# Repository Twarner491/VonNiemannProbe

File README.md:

# Von Niemann Probe
### Devoloped by [Teddy Warner](https://teddywarner.org/About-Me/about/) and [Jack Hollingsworth](http://fabacademy.org/2021/labs/charlotte/students/jack-hollingsworth/about/).

**An AVR-based Bluetooth telegraphing shoe insole that lets you play chess in the way Hans Niemann has been accused!** This project is our contribution to the ongoing investigation into the Hans Niemann / Magnus Carlsen cheating scandal and tests the feasibility of creating and using an over-the-board chess cheating aid.

### Check out the Von Niemann Probe's documentation on [TeddyWarner.org](https://teddywarner.org/Projects/VonNiemannProbe/)!

**© Teddy Warner & Jack Hollingsworth- 2022**
> This work may be reproduced, modified, distributed, performed, and displayed for any purpose,
> but must acknowledge Teddy Warner. Copyright is retained and must be preserved. 
> The work is provided as is; no warranty is provided, and users accept all liability.

### Sponsor -

## Python Dependencies - 

Various Python dependencies are needed to run the VNPFinal.py script, but overall the installation is pretty lightweight. The only change that needs to be made locally is the path of your stockfish .exe, which must be downloaded from [here](https://stockfishchess.org/download/) prior to use. Any version of Stockfish should work, but we have only tested on the latest version (Version 15). 
<br/><br/>
The outgoing COM port of the Bluetooth module must be updated, this can be found in device manager in all Windows 7+ machines. 
Install commands for all Python dependencies are below, any release past Python 3.7 will work.

```python
pip install stockfish
pip install python-chess
pip install pyserial
pip install regex
```

## Sources -
- [https://www.npr.org/2022/10/21/1130442319/hans-niemann-sues-magnus-carlsen-for-100-million-accusing-him-of-defamation](https://www.npr.org/2022/10/21/1130442319/hans-niemann-sues-magnus-carlsen-for-100-million-accusing-him-of-defamation)
- [https://youtu.be/eg5G1A_mTFg](https://youtu.be/eg5G1A_mTFg)
- [https://twitter.com/hansmokeniemann](https://twitter.com/hansmokeniemann)
- [https://futurism.com/von-neumann-probe](https://futurism.com/von-neumann-probe)
- [https://ww1.microchip.com/downloads/en/DeviceDoc/ATtiny212-412-DataSheet-DS40001911B.pdf](https://ww1.microchip.com/downloads/en/DeviceDoc/ATtiny212-412-DataSheet-DS40001911B.pdf)
- [https://components101.com/sites/default/files/component_datasheet/HC06%20Bluetooth%20Module%20Datasheet.pdf](https://components101.com/sites/default/files/component_datasheet/HC06%20Bluetooth%20Module%20Datasheet.pdf)
- [https://components101.com/wireless/hc-06-bluetooth-module-pinout-datasheet](https://components101.com/wireless/hc-06-bluetooth-module-pinout-datasheet)
- [http://www.sizecharter.com/clothing-fit-and-measurement/understanding-shoe-sizing](http://www.sizecharter.com/clothing-fit-and-measurement/understanding-shoe-sizing)
- [https://www.researchgate.net/figure/The-Mean-of-Absolute-in-mm-and-Relative-in-FL-Foot-Dimensions-for-Both-Genders-a_tbl2_327021689](https://www.researchgate.net/figure/The-Mean-of-Absolute-in-mm-and-Relative-in-FL-Foot-Dimensions-for-Both-Genders-a_tbl2_327021689)
- [https://www.researchgate.net/figure/Measurements-of-the-foot-and-the-inner-shoe-dimensions-a-Foot-Length-FL-and-Foot_fig5_280976288](https://www.researchgate.net/figure/Measurements-of-the-foot-and-the-inner-shoe-dimensions-a-Foot-Length-FL-and-Foot_fig5_280976288)
- [https://www.protalus.com/blogs/news/how-to-measure-feet](https://www.protalus.com/blogs/news/how-to-measure-feet)
- [https://www.magnuscarlsen.com/en](https://www.magnuscarlsen.com/en)
- [https://twitter.com/MagnusCarlsen](https://twitter.com/MagnusCarlsen)
- [https://www.chess.com/blog/CHESScom/hans-niemann-report](https://www.chess.com/blog/CHESScom/hans-niemann-report)
- [https://www.bbc.com/news/world-63010107](https://www.bbc.com/news/world-63010107)
- [https://www.bbc.com/news/world-63043023](https://www.bbc.com/news/world-63043023)
- [https://www.youtube.com/watch?v=CJZuT-_kij0&t=593s](https://www.youtube.com/watch?v=CJZuT-_kij0&t=593s)
- [https://cse.buffalo.edu/~regan/chess/fidelity/data/Niemann/](https://cse.buffalo.edu/~regan/chess/fidelity/data/Niemann/)
- [https://twitter.com/MagnusCarlsen/status/1574482694406565888?s=20](https://twitter.com/MagnusCarlsen/status/1574482694406565888?s=20)
- [https://www.wsj.com/articles/chess-cheating-hans-niemann-report-magnus-carlsen-11664911524](https://www.wsj.com/articles/chess-cheating-hans-niemann-report-magnus-carlsen-11664911524)
- [https://storage.courtlistener.com/recap/gov.uscourts.moed.198608/gov.uscourts.moed.198608.1.0.pdf](https://storage.courtlistener.com/recap/gov.uscourts.moed.198608/gov.uscourts.moed.198608.1.0.pdf)
- [https://frontofficesports.com/top-chess-player-platform-join-forces-in-82-9m-deal/](https://frontofficesports.com/top-chess-player-platform-join-forces-in-82-9m-deal/)
- [https://www.washingtonpost.com/sports/2022/10/05/chess-com-investigation-cheating-hans-niemann-magnus-carlsen/](https://www.washingtonpost.com/sports/2022/10/05/chess-com-investigation-cheating-hans-niemann-magnus-carlsen/)

---
- [Fork this repository](https://github.com/Twarner491/VonNiemannProbe/fork)
- [Watch this repo](https://github.com/Twarner491/VonNiemannProbe/subscription)
- [Create issue](https://github.com/Twarner491/VonNiemannProbe/issues/new)

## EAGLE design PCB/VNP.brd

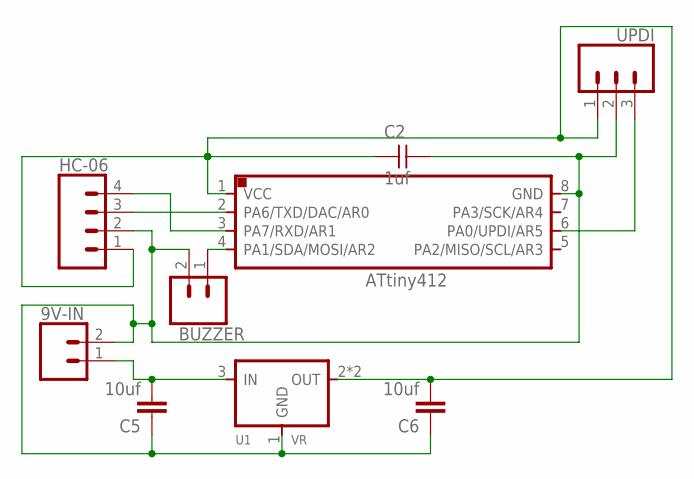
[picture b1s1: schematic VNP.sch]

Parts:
9V-IN: CONN_02PTH3; 1X02_LONGPADS
BUZZER: CONN_02LOCK_LONGPADS; 1X02_LOCK_LONGPADS
C2: 1uf; C1206
C5, C6: 10uf; 1206
HC-06: CONN_04POLAR; MOLEX-1X4
U1: VR; SOT223
U$1: UC_ATTINY412SI; SOIC8
UPDI: CONN_03SMD_RA_MALE; 1X03_SMD_RA_MALE

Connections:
5V: C2.1, C6.2, HC-06.1, U1.2 (OUT), U1.4 (OUT), U$1.1 (VCC), UPDI.1
BUZZER: BUZZER.1, U$1.4 (PA1/SDA/MOSI/AR2)
GND: 9V-IN.2, BUZZER.2, C2.2, C5.1, C6.1, HC-06.2, U1.1 (GND), U$1.8 (GND), UPDI.2
RX: HC-06.4, U$1.3 (PA7/RXD/AR1)
TX: HC-06.3, U$1.2 (PA6/TXD/DAC/AR0)
UPDI: U$1.6 (PA0/UPDI/AR5), UPDI.3
VCC: 9V-IN.1, C5.2, U1.3 (IN)

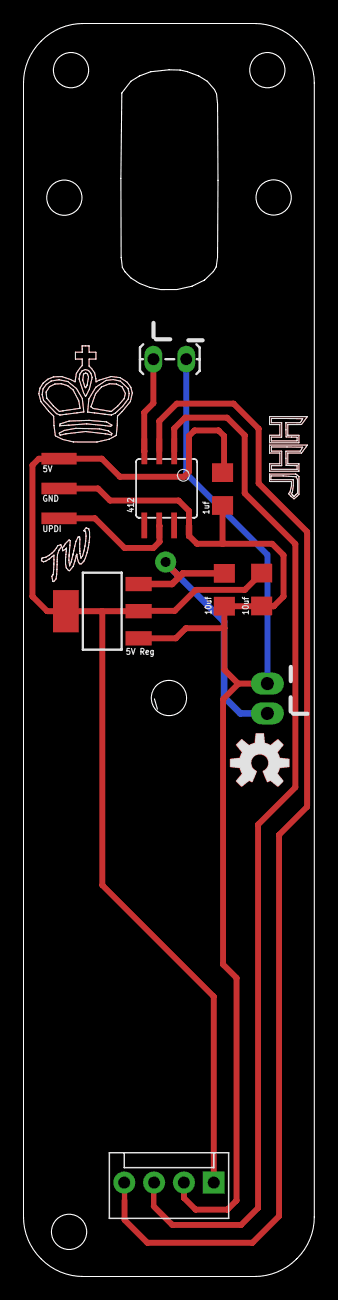
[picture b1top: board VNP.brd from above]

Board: 2 copper layers, 24.8 x 106.7 mm, 11 parts (0 on the bottom side), 7 nets.

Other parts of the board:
U$2: OSHW-LOGO-M_COPPER
U$3: OSHW-LOGO-M

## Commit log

2022-10-21 chess engine updates
2022-10-21 link fix
2022-10-21 configured butt plug interface to better regulate arousal and prolong orgasmic activity
2022-10-21 LICENSE Update
2022-10-22 basic sending and receiving between python and hc-06 bluetooth
2022-10-22 file sorting
2022-10-22 ReadME Updates
2022-10-22 Source Addation
2022-10-22 final arduino and python code
2022-10-22 Sources Addation
2022-10-22 Source List Fix
2022-10-22 NPR Inclusion
2022-10-22 Source fix
2022-10-22 Insole Inital
2022-10-23 PCB Push
2022-10-23 insole electronic intigration
2022-10-23 small updates to receiving, added morse learning
2022-10-24 PCB Logo Updates
2022-10-24 Update receiveViaBluetooth.ino
    updated several functions to make all of the delays proportional to the dot time, so everything scales relative to dots rather than having to change multiple values.
2022-10-24 Insole Parametric Update & file Structure Overhaul - Check local compilation upon merge
2022-10-24 Code Copyrights and Arduino Lib Inclusion
2022-10-25 various small updates
2022-10-25 Update README.md
    added description of python dependencies and local changes that need to be made in VNPFinal.py for the device to function, included commands to download all dependencies.
2022-10-25 remove undesireable folder
2022-10-25 Update VNPFinal.py
    added checks for player victory to player on white and player on black
2022-10-25 Update README.md
    highlight python syntax in readme
2022-10-25 Update README.md
    fix syntax highlighting
2022-10-25 Update README.md
    formatting test
2022-10-25 Update README.md
    concision and detail updates
2022-10-27 PCB Dim Update
2022-10-27 pip install dependency update
2022-10-27 Updated StockFish URL to universal
2022-10-28 use relative path of engine stored locally
2022-10-28 file name updates
2022-10-28 remove excessive checkmate debug prints
2022-10-28 arduino bluetooth code updates
2022-10-28 c++ updates
2022-10-28 final python comment proliferation to enhance readability and understanding
2022-11-06 Board Fix
2022-11-10 Insole Updates
2022-11-13 Final PCB, Gerber Files & Final Reciever Code
2022-11-14 sources push
2022-11-15 new translation
2022-11-15 updated morse translation code
2022-11-15 re-add debug
2022-11-18 added shorter delay when funny encoding used, allows for faster relay of moves
2022-12-22 Gen 2 Push
2022-12-23 Comment fix
2023-01-05 quotation changes
2023-01-09 Almost final CAD
2023-01-15 Boost Converter CAD Updates
2023-01-16 Update Sources & link to doc
2023-01-28 Source Update
2023-02-02 modified
    Refactor and reformat for clarity
2023-04-07 Refactored and organized for increased readability
2023-04-08 funnyEncoding formatting and contributor addition
2023-04-08 Revert "Prettify & increase the quality of the code"
2023-04-08 Update VNPFinal.py w/ contribution
2023-06-16 test

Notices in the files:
parts and their libraries:
SparkFun-Connectors: Licensing: Creative Commons ShareAlike 4.0 International - https://creativecommons.org/licenses/by-sa/4.0
01_SparkFun: Licensing: CC v3.0 Share-Alike You are welcome to use this library for commercial purposes.
